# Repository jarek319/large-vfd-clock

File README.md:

# large-vfd-clock
The largest VFDs I can get my hands on make a really nice clock!

The ILC1-1/8L was another interesting specimen I found while trawling ebay for strange displays.

4 of them with another VFD tube for the colon connect to a Wifi-enabled microcontroller for timekeeping.

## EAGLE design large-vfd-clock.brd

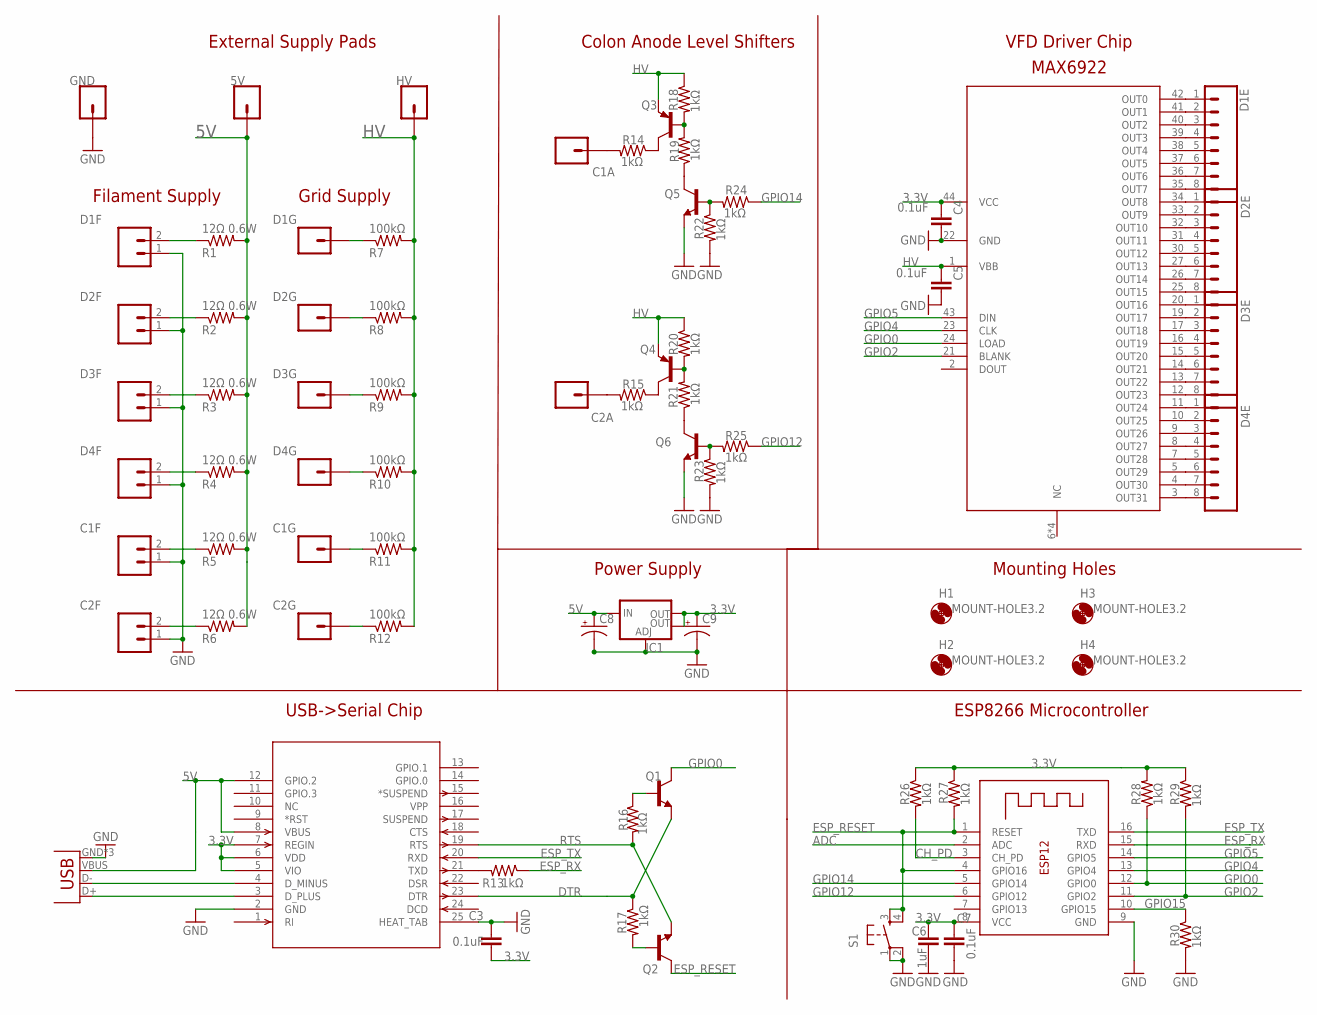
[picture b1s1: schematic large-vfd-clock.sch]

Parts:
5V: M01PTH_LONGPAD; 1X01_LONGPAD
C1A, C1G, C2A, C2G: M01PTH_LONGPAD; 1X01_LONGPAD
C1F, C2F: M02LOCK_LONGPADS; 1X02_LOCK_LONGPADS
C3, C4, C5, C7: 0.1uF; C025-024X044
C6: 1uF; C025-024X044
C8, C9: CPOL-USE2,5-6E; E2,5-6E
D1E, D2E, D3E, D4E: M08LOCK_LONGPADS; 1X08_LOCK_LONGPADS
D1F, D2F, D3F, D4F: M02LOCK_LONGPADS; 1X02_LOCK_LONGPADS
D1G, D2G, D3G, D4G: M01PTH_LONGPAD; 1X01_LONGPAD
GND: M01PTH_LONGPAD; 1X01_LONGPAD
H1, H2, H3, H4: MOUNT-HOLE3.2; 3,2
HV: M01PTH_LONGPAD; 1X01_LONGPAD
IC1: V_REG_LM1117SOT223; SOT223
JP8: SPARKFUN-CONNECTORS_USB-MICROB
Q1, Q2, Q5, Q6: MMBT2222A; TO-92
Q3, Q4: MMBT3906; TO92
R1, R2, R3, R4, R5, R6: 12Ω 0.6W; 0207/7
R7, R8, R9, R10, R11, R12: 100kΩ; 0207/7
R13, R14, R15, R16, R17, R18, R19, R20, R21, R22, R23, R24, R25, R26, R27, R28, R29, R30: 1kΩ; 0207/7
S1: TAC_SWITCHPTH; TACTILE-PTH
U1: CP2104-GM; QFN24_4X4
U2: MAX6922; PLCC44
X1: ESP-12

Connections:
3.3V: C3.2, C4.1, C6.1, C7.1, C9.+, IC1.2 (OUT), IC1.4 (OUT), R26.1, R27.1, R28.2, R29.1, U1.5 (VIO), U1.6 (VDD), U1.7 (REGIN), U2.44 (VCC), X1.8 (VCC)
5V: 5V.1, C8.+, IC1.3 (IN), JP8.VBUS, R1.2, R2.2, R3.2, R4.2, R5.2, R6.2, U1.8 (VBUS), U1.12 (GPIO.2)
ADC: X1.2 (ADC)
CH_PD: R26.2, X1.3 (CH_PD)
DTR: Q1.1 (E), R17.1, U1.23 (DTR)
D_N1: JP8.D-, U1.4 (D_MINUS)
D_P1: JP8.D+, U1.3 (D_PLUS)
ESP_RESET: Q2.3 (C), R27.2, S1.3, S1.4, X1.1 (RESET), X1.4 (GPIO16)
ESP_RX: R13.1, X1.15 (RXD)
ESP_TX: U1.20 (RXD), X1.16 (TXD)
GND: C1F.1, C2F.1, C3.1, C4.2, C5.2, C6.2, C7.2, C8.-, C9.-, D1F.1, D2F.1, D3F.1, D4F.1, GND.1, IC1.1 (ADJ), JP8.GND, JP8.MT1 (GND), JP8.MT2 (GND), Q5.1 (E), Q6.1 (E), R22.2, R23.2, R30.2, S1.1, S1.2, U1.2 (GND), U1.25 (HEAT_TAB), U2.22 (GND), X1.9 (GND)
GPIO0: Q1.3 (C), R28.1, U2.24 (LOAD), X1.12 (GPIO0)
GPIO2: R29.2, U2.21 (BLANK), X1.11 (GPIO2)
GPIO4: U2.23 (CLK), X1.13 (GPIO4)
GPIO5: U2.43 (DIN), X1.14 (GPIO5)
GPIO12: R25.1, X1.6 (GPIO12)
GPIO14: R24.1, X1.5 (GPIO14)
GPIO15: R30.1, X1.10 (GPIO15)
HV: C5.1, HV.1, Q3.3 (E), Q4.3 (E), R7.2, R8.2, R9.2, R10.2, R11.2, R12.2, R18.1, R20.1, U2.1 (VBB)
unnamed: R13.2, U1.21 (TXD)
unnamed: D1E.1, U2.42 (OUT0)
unnamed: Q1.2 (B), R16.1
unnamed: Q2.2 (B), R17.2
unnamed: D1E.2, U2.41 (OUT1)
unnamed: D1E.3, U2.40 (OUT2)
unnamed: D1E.4, U2.39 (OUT3)
unnamed: D1E.5, U2.38 (OUT4)
unnamed: D1E.6, U2.37 (OUT5)
unnamed: D1E.7, U2.36 (OUT6)
unnamed: D1E.8, U2.35 (OUT7)
unnamed: D2E.1, U2.34 (OUT8)
unnamed: D2E.2, U2.33 (OUT9)
unnamed: D2E.3, U2.32 (OUT10)
unnamed: D2E.4, U2.31 (OUT11)
unnamed: D2E.5, U2.30 (OUT12)
unnamed: D2E.6, U2.27 (OUT13)
unnamed: D2E.7, U2.26 (OUT14)
unnamed: D2E.8, U2.25 (OUT15)
unnamed: D3E.1, U2.20 (OUT16)
unnamed: D3E.2, U2.19 (OUT17)
unnamed: D3E.3, U2.17 (OUT18)
unnamed: D3E.4, U2.16 (OUT19)
unnamed: D3E.5, U2.15 (OUT20)
unnamed: D3E.6, U2.14 (OUT21)
unnamed: D3E.7, U2.13 (OUT22)
unnamed: D3E.8, U2.12 (OUT23)
unnamed: D4E.1, U2.11 (OUT24)
unnamed: D4E.2, U2.10 (OUT25)
unnamed: D4E.3, U2.9 (OUT26)
unnamed: D4E.4, U2.8 (OUT27)
unnamed: D4E.5, U2.7 (OUT28)
unnamed: D4E.6, U2.5 (OUT29)
unnamed: D4E.7, U2.4 (OUT30)
unnamed: D4E.8, U2.3 (OUT31)
unnamed: Q5.2 (B), R22.1, R24.2
unnamed: Q6.2 (B), R23.1, R25.2
unnamed: D4G.1, R10.1
unnamed: D3G.1, R9.1
unnamed: D2G.1, R8.1
unnamed: D1G.1, R7.1
unnamed: C2G.1, R12.1
unnamed: C1G.1, R11.1
unnamed: C1F.2, R5.1
unnamed: C2F.2, R6.1
unnamed: Q4.1 (C), R15.1
unnamed: Q3.1 (C), R14.1
unnamed: C1A.1, R14.2
unnamed: C2A.1, R15.2
unnamed: D1F.2, R1.1
unnamed: D2F.2, R2.1
unnamed: D3F.2, R3.1
unnamed: D4F.2, R4.1
unnamed: Q5.3 (C), R19.1
unnamed: Q3.2 (B), R18.2, R19.2
unnamed: Q6.3 (C), R21.1
unnamed: Q4.2 (B), R20.2, R21.2
RTS: Q2.1 (E), R16.2, U1.19 (RTS)

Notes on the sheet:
Filament Supply
Grid Supply
External Supply Pads
Colon Anode Level Shifters
Mounting Holes
VFD Driver Chip
MAX6922
Power Supply
USB->Serial Chip
ESP8266 Microcontroller

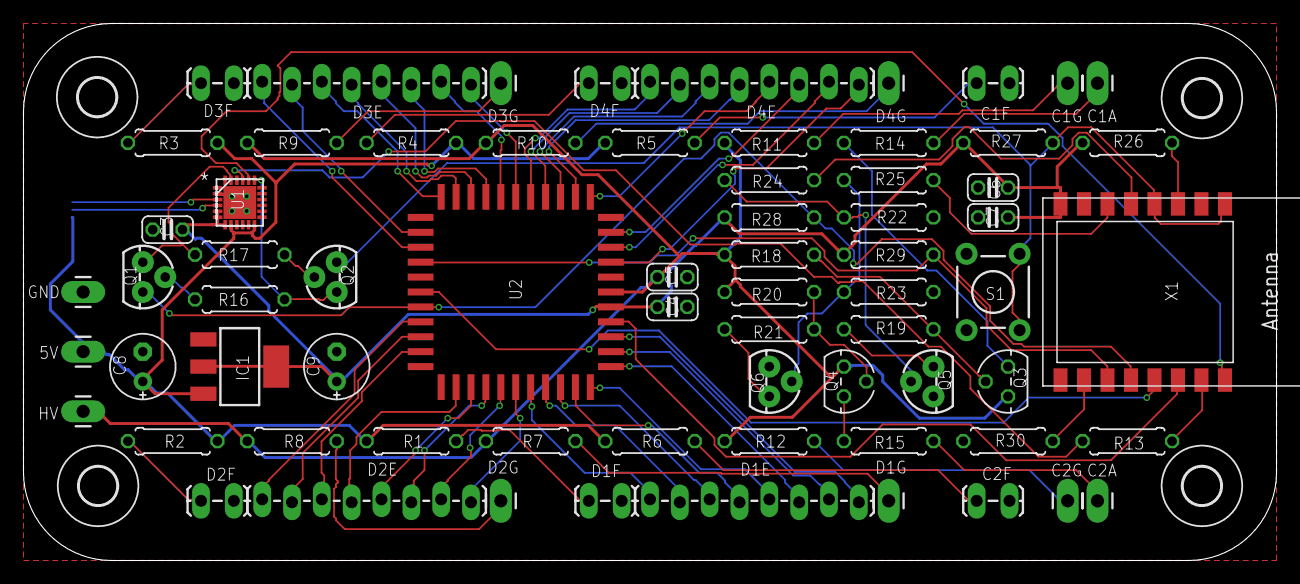
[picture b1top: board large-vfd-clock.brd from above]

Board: 2 copper layers, 106.7 x 45.7 mm, 74 parts (1 on the bottom side), 76 nets.

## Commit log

2018-07-05 design tested: working

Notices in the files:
parts and their libraries:
SparkFun-PowerIC: Licensing: CC v3.0 Share-Alike You are welcome to use this library for commercial purposes.
